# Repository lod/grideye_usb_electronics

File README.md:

GridEye USB Board
=================

This board is designed to allow a USD host to connect to a Panasonic GridEye sensor.

The files were generated by and can be opened by KiCad.

This is version 1 of the board. The PCBs have been sent off to be fabricated, grideye_usb_two_sided_gerbers.zip contains a set of gerbers suitable for use by OSHPark.

The design **probably** does not work. The parts have never been placed on the board, the board has never been powered up, no firmware has been written... the availability of this design should be considered an academic curiosity, not something to use.

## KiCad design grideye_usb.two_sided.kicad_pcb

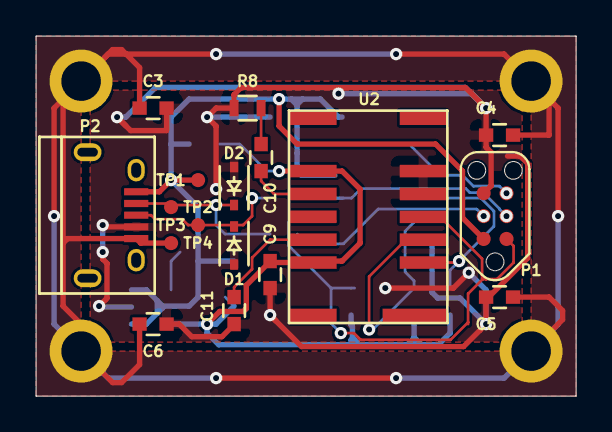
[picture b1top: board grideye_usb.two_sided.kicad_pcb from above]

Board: 2 copper layers, 30.0 x 20.0 mm, 31 parts (0 on the bottom side), 16 nets.

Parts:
C1: 2.2uF; SMD-1210_Pol
C2: 470pF; C_0603
C3, C4, C5, C6: DNF; C_0603
C7, C9: 10uF; C_0603
C8: 0.1uF; C_0603
C10: 1uF; C_0603
C11: 1.5uF; C_0603
D1, D2: 3V6; SOD-323
IC1: ATTINY45-S; SOIC-8_3.9x4.9mm_Pitch1.27mm
P1: TC2030-IDC; TC2030-NL_SMALL
P2: USB_B; USB_Micro-B
R1: DNF; R_0603
R2: 1k5; R_0603
R3, R4: 68R; R_0603
R5, R6, R7: 10k; R_0603
R8: 20R; R_0603
R9: 4k7; R_0603
TP1, TP2, TP3, TP4: Measurement_Point_Round-SMD-Pad_Small
U1: MIC5205-x.x; SOT-23-5
U2: GridEye; AMG8851

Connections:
/INT: IC1.6, P1.1, R7.2, U2.4
/MOSI: IC1.5, P1.4, R3.2
/RST: IC1.1, P1.5, R9.2
/SCK: IC1.7, P1.3, R4.2
/SCL: IC1.3, R6.2, U2.3
/SDA: IC1.2, R5.2, U2.2
/USB_N: D2.1, P2.2, R2.2, R3.1, TP2.1
/USB_P: D1.1, P2.3, R4.1, TP3.1
GND: C1.2, C2.2, C3.2, C4.1, C5.2, C6.1, C7.2, C8.2, C9.2, C11.2, D1.2, D2.2, IC1.4, P1.6, P2.4, R8.2, U1.2, U2.5, U2.6
GNDPWR: C3.1, C4.2, C5.1, C6.2, P2.5, TP4.1
unnamed: C2.1, U1.4
unnamed: C10.1, U2.10
unnamed: C10.2, R8.1
unnamed: C11.1, U2.12
vsens: C1.1, C9.1, R1.1, R5.1, R6.1, R7.1, U1.5, U2.9, U2.13
vusb: C7.1, C8.1, IC1.8, P1.2, P2.1, R1.2, R2.1, R9.1, TP1.1, U1.1, U1.3

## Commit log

2016-04-15 Sanitise history for upload
    Because we all like the ability to rewrite the past and remove our
    mistakes.
